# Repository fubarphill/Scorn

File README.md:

# Scorn
A split ergo keyboard based on the Corne (crkbd) by Foostan

Increased pinky stagger, similar to Cantor/Piantor but with added splay on pinky columns.

Built using Ergogen.

## How to clone this repo

You must also include the footprints submodule from ceoloide. Please clone with --recursive mode:

##
    git clone --recursive git@github.com:fubarphill/Scorn.git

## Thanks and recognition

* [foostan](https://github.com/foostan/crkbd) - for the awesome Corne (Crkbd)
* [beekeeb](https://github.com/beekeeb/piantor) - for the Piantor, which made me realise I need a bigger stagger for my pinkies
* The [Ergogen](https://github.com/ergogen/ergogen) team - for the amazing tool
* [ceoloide](https://github.com/ceoloide) - for the extra ergogen footprints
* [FlatFootFox](https://flatfootfox.com/ergogen-part1-units-points/) - for the best Ergogen guide I've seen

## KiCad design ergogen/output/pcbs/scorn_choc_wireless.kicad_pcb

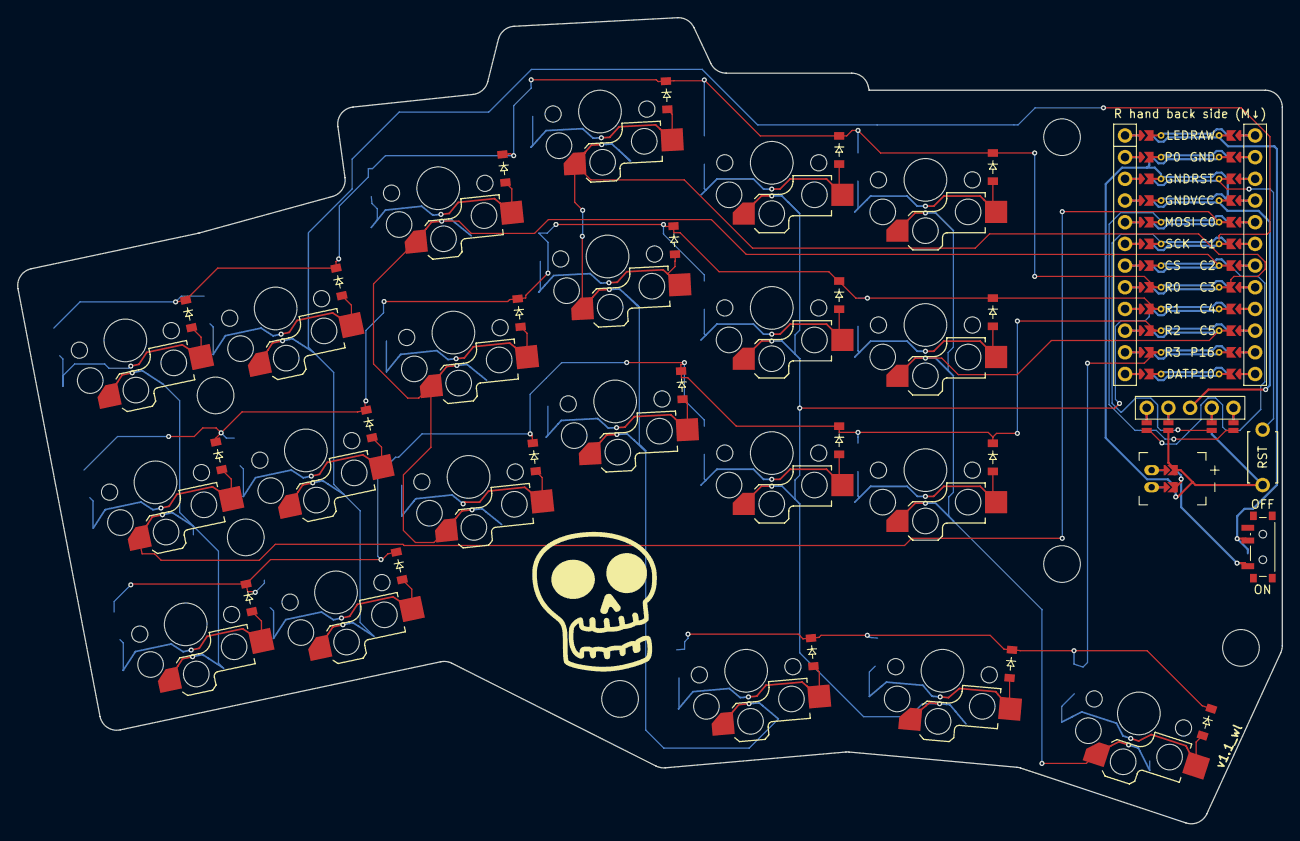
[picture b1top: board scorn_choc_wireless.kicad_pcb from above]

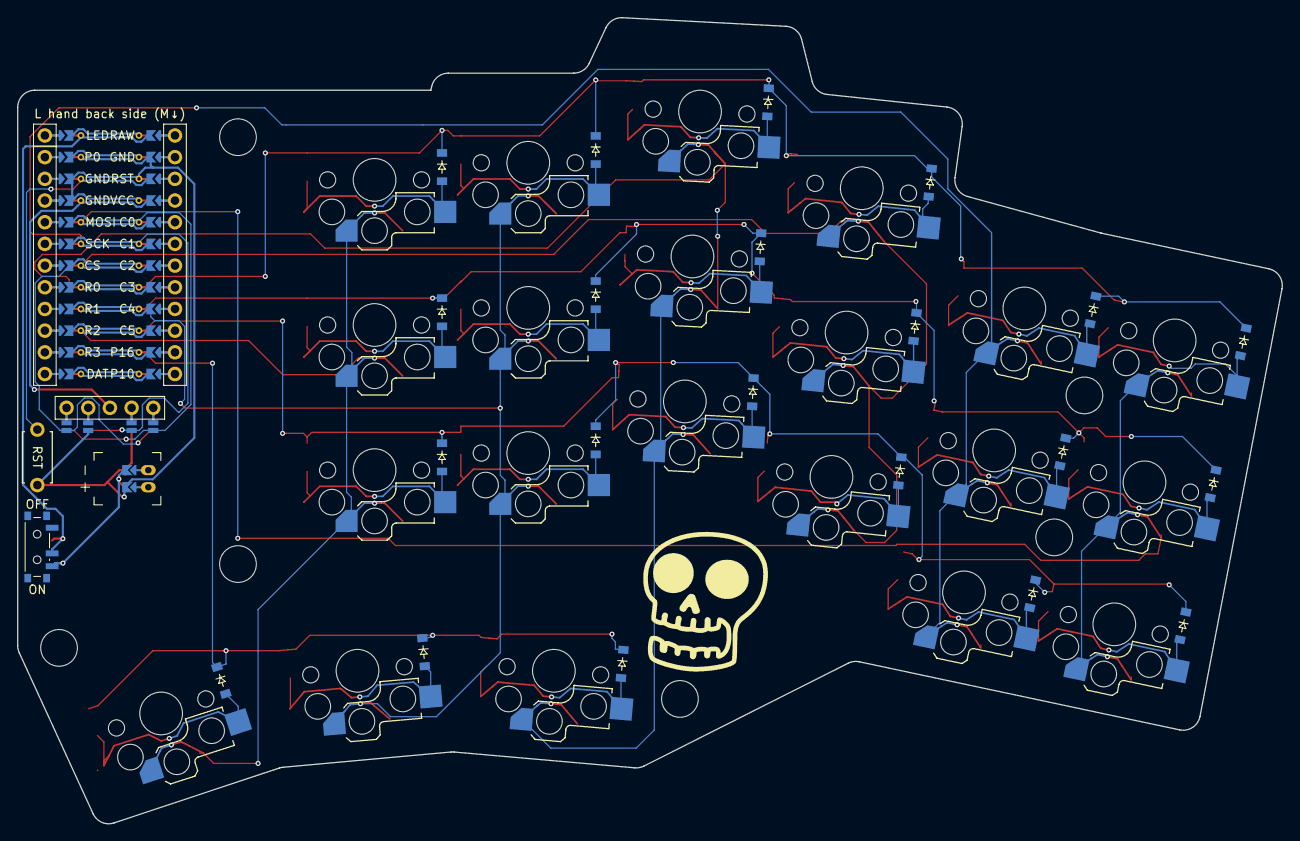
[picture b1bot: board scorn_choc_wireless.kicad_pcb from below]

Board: 2 copper layers, 148.1 x 94.4 mm, 76 parts (43 on the bottom side), 45 nets.

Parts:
BAT1: battery_connector_jst_ph_2
D1, D2, D3, D4, D5, D6, D7, D8, D9, D10, D11, D12, D13, D14, D15, D16, D17, D18, D19, D20, D21, D22, D23, D24, D25, D26, D27, D28, D29, D30, D31, D32, D33, D34, D35, D36, D37, D38, D39, D40, D41, D42: diode_tht_sod123
DISP1: display_nice_view
LOGO_B: LOGO; logo_sml
LOGO_F: LOGO; logo_sml_flp
MCU1: mcu_nice_nano
MH1, MH2, MH3, MH4, MH5, MH6: mounting_hole_npth
PWR1: power_switch_smd_side
RST1: reset_switch_tht_top
SW1, SW2, SW3, SW4, SW5, SW6, SW7, SW8, SW9, SW10, SW11, SW12, SW13, SW14, SW15, SW16, SW17, SW18, SW19, SW20, SW21: switch_choc_v1_v2

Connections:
BAT1_1: BAT1.11, BAT1.21, BAT1.31
BAT1_2: BAT1.12, BAT1.22, BAT1.32
BAT_P: BAT1.1, PWR1.1, PWR1.3
C0: MCU1.105, SW1.1, SW2.1, SW3.1
C1: MCU1.106, SW4.1, SW5.1, SW6.1
C2: MCU1.107, SW7.1, SW8.1, SW9.1
C3: MCU1.108, SW10.1, SW11.1, SW12.1, SW19.1
C4: MCU1.109, SW13.1, SW14.1, SW15.1, SW20.1
C5: MCU1.110, SW16.1, SW17.1, SW18.1, SW21.1
CS: DISP1.10, DISP1.20, MCU1.118
DISP1_1: DISP1.1, DISP1.14, DISP1.27
DISP1_2: DISP1.2, DISP1.15, DISP1.26
DISP1_4: DISP1.4, DISP1.16, DISP1.25
DISP1_5: DISP1.5, DISP1.17, DISP1.24
GND: BAT1.2, DISP1.11, DISP1.21, MCU1.102, MCU1.121, MCU1.122, RST1.2
MOSI: DISP1.13, DISP1.23, MCU1.120
R0: D3.1, D6.1, D9.1, D12.1, D15.1, D18.1, D24.1, D27.1, D30.1, D33.1, D36.1, D39.1, MCU1.117
R1: D2.1, D5.1, D8.1, D11.1, D14.1, D17.1, D23.1, D26.1, D29.1, D32.1, D35.1, D38.1, MCU1.116
R2: D1.1, D4.1, D7.1, D10.1, D13.1, D16.1, D22.1, D25.1, D28.1, D31.1, D34.1, D37.1, MCU1.115
R3: D19.1, D20.1, D21.1, D40.1, D41.1, D42.1, MCU1.114
RAW: MCU1.101, PWR1.2
RST: MCU1.103, RST1.1
SCK: DISP1.12, DISP1.22, MCU1.119
VCC: DISP1.3, MCU1.104
index_bottom: D13.2, D34.2, SW13.2
index_home: D14.2, D35.2, SW14.2
index_top: D15.2, D36.2, SW15.2
inner_bottom: D16.2, D37.2, SW16.2
inner_cluster: D19.2, D40.2, SW19.2
inner_home: D17.2, D38.2, SW17.2
inner_top: D18.2, D39.2, SW18.2
mid_cluster: D20.2, D41.2, SW20.2
middle_bottom: D10.2, D31.2, SW10.2
middle_home: D11.2, D32.2, SW11.2
middle_top: D12.2, D33.2, SW12.2
outer_bottom: D1.2, D22.2, SW1.2
outer_cluster: D21.2, D42.2, SW21.2
outer_home: D2.2, D23.2, SW2.2
outer_top: D3.2, D24.2, SW3.2
pinky_bottom: D4.2, D25.2, SW4.2
pinky_home: D5.2, D26.2, SW5.2
pinky_top: D6.2, D27.2, SW6.2
ring_bottom: D7.2, D28.2, SW7.2
ring_home: D8.2, D29.2, SW8.2
ring_top: D9.2, D30.2, SW9.2

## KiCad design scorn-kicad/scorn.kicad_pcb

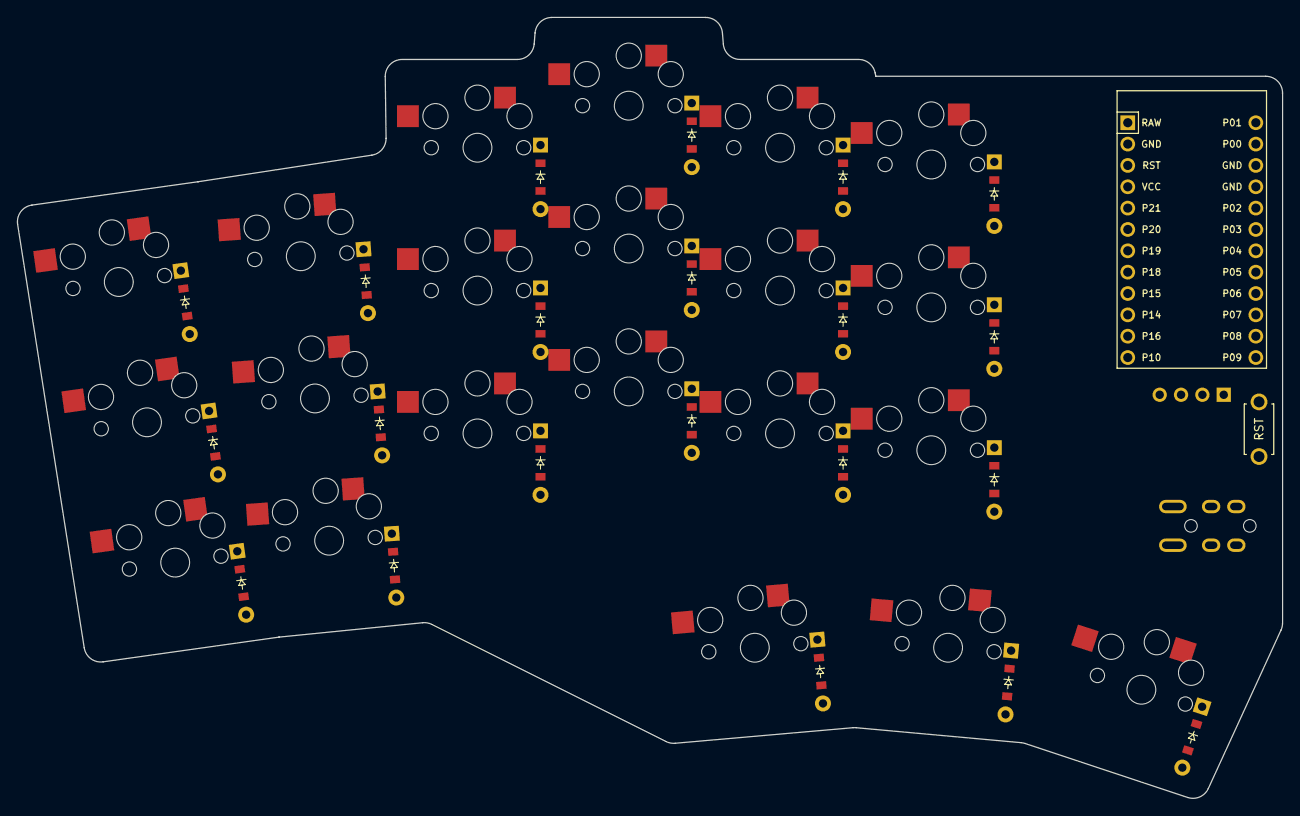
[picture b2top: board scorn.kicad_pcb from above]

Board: 2 copper layers, 150.5 x 92.9 mm, 46 parts (0 on the bottom side), 27 nets, no tracks yet.

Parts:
D1, D2, D3, D4, D5, D6, D7, D8, D9, D10, D11, D12, D13, D14, D15, D16, D17, D18, D19, D20, D21: ComboDiode
MCU1: ProMicro
OLED1: OLED; OLED_headers
RST1: reset_switch_tht_top
S1, S2, S3, S4, S5, S6, S7, S8, S9, S10, S11, S12, S13, S14, S15, S16, S17, S18, S19, S20, S21: PG1350
TRRS1: trrs_pj320a (reversible, symmetric)

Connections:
GND: MCU1.2, MCU1.15, MCU1.16, OLED1.1, RST1.2, TRRS1.2
P2: MCU1.17, OLED1.4
P3: MCU1.18, OLED1.3
P9: MCU1.24, TRRS1.3
RST: MCU1.3, RST1.1
VCC: MCU1.4, OLED1.2, TRRS1.4
index_bottom: D13.2, S13.2
index_home: D14.2, S14.2
index_top: D15.2, S15.2
inner_bottom: D16.2, S16.2
inner_cluster: D19.2, S19.2
inner_home: D17.2, S17.2
inner_top: D18.2, S18.2
mid_cluster: D20.2, S20.2
middle_bottom: D10.2, S10.2
middle_home: D11.2, S11.2
middle_top: D12.2, S12.2
outer_bottom: D1.2, S1.2
outer_cluster: D21.2, S21.2
outer_home: D2.2, S2.2
outer_top: D3.2, S3.2
pinky_bottom: D4.2, S4.2
pinky_home: D5.2, S5.2
pinky_top: D6.2, S6.2
ring_bottom: D7.2, S7.2
ring_home: D8.2, S8.2
ring_top: D9.2, S9.2

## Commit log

2024-09-22 initial upload
2024-09-22 added footprints submodule
2024-09-23 Added metadata to config.yaml
2024-09-29 pcb layout complete
2024-10-02 stagger and splay rework
2024-10-02 adding files
2024-10-02 cleaning up files
2024-11-30 tidied up and collated v1 files
2024-12-16 update footprints submodule
2024-12-16 added v1.1
2024-12-16 updated v1.1
